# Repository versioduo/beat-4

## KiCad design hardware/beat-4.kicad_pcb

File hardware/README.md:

# beat-4
🧲 4 Channel Solenoid Controller

## Schematic
[PDF](beat-4.pdf)

## Bill Of Materials
[Interactive BOM](https://versioduo.com/view?url=https://raw.githubusercontent.com/versioduo/beat-4/refs/heads/main/hardware/beat-4-bom.html)

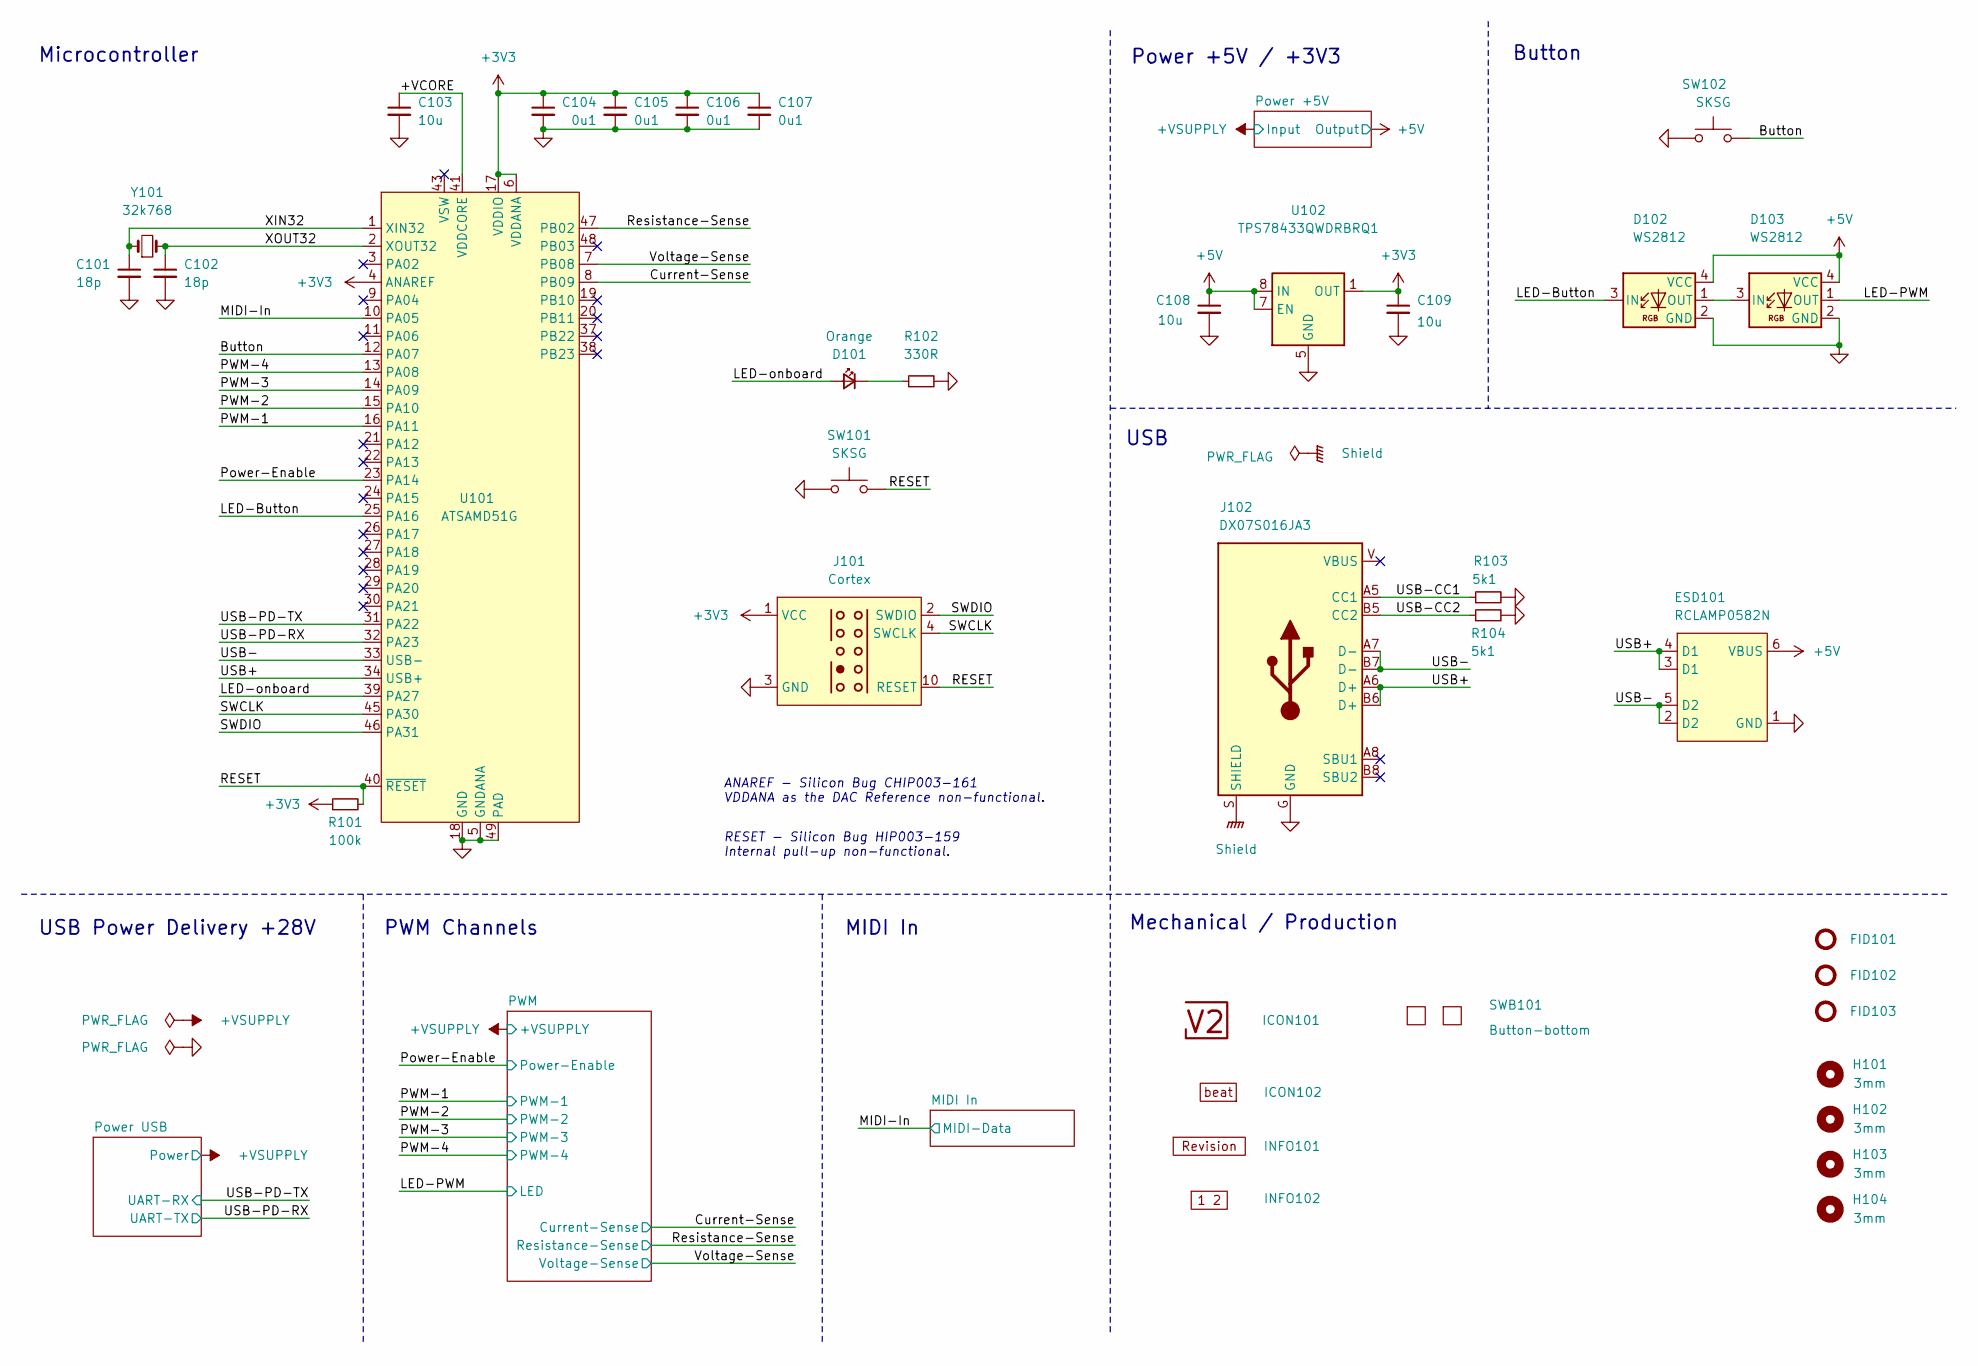
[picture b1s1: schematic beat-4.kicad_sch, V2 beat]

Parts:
C101, C102: 18p; C_1608; Rating 50V; Mouser 810-CGA3E2C0G1H180J
C103: 10u; C_1608; Rating 10V; Mouser 810-C1608X6S1A106M
C104, C105, C106, C107: 0u1; C_1608; Rating 50V; Mouser 810-CGA3E2X7R1H104MA
C108, C109: 10u; C_2012; Rating 25V; Mouser 810-C2012X5R1E106K
D101: Orange; LED_1608; Rating 605nm; Mouser 755-SML-D12D1WT86
D102, D103: WS2812; WS2812-2020; Rating 15mA; LCSC C965555
ESD101: RCLAMP0582N; SLP1210N6; Rating 20kV; Mouser 947-RCLAMP0582N.TCT
FID101, FID102, FID103: Fiducial_Paste; Fiducial_0.5mm_Mask1mm_Paste
H101, H102, H103, H104: 3mm; MountingHole_3mm
ICON101: V2-logo; Logo_Small
ICON102: Board_axis; Board_beat_Small
INFO101: Revision
INFO102: Layer_Numbers-4
J101: Cortex
J102: DX07S016JA3; JAE_DX07S016JA3; Rating USB2.0; Mouser 656-DX07S016JA3R1500
R101: 100k; R_1608; Rating 100mW; Mouser 71-CRCW0603100KFKEAC
R102: 330R; R_1608; Rating 100mW; Mouser 71-CRCW0603330RFKEAC
R103, R104: 5k1; R_1608; Rating 100mW; Mouser 71-CRCW06035K10FKEAC
SW101, SW102: SKSG; Rating 1.6N; Mouser 688-SKSGACE010
SWB101: Button-bottom; PCB_Button-bottom
U101: ATSAMD51G; QFN-48-1EP_7x7mm_P0.5mm_EP5.45x5.45mm_ThermalVias; Rating Cortex-M4F; Mouser 556-ATSAMD51G19AMU
U102: TPS78433QWDRBRQ1; VSON-8-1_3x3mm_P0.65_EP1.65x2.4mm; Rating 300mA; Mouser 595-TPS78433QWDRBRQ1
Y101: 32k768; Crystal_SMD_3215-2Pin_3.2x1.5mm; Rating 10ppm; Mouser 815-ABS0716632.768KT

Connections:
+3V3: C104.1, C105.1, C106.1, C107.1, C109.1, J101.1 (VCC), R101.1, U101.4 (ANAREF), U101.6 (VDDANA), U101.17 (VDDIO), U101.36 (VDDIO), U101.44 (VDDIO), U102.1 (OUT); also elsewhere on the board
+5V: C108.1, D102.4 (VCC), D103.4 (VCC), ESD101.6 (VBUS), U102.6 (EN), U102.7 (EN), U102.8 (IN); also elsewhere on the board
/+VCORE: C103.1, U101.41 (VDDCORE)
/Button: SW102.2, U101.12 (PA07)
/Current-Sense: U101.8 (PB09); also elsewhere on the board
/LED-Button: D102.3 (IN), U101.25 (PA16)
/LED-PWM: D103.1 (OUT); also elsewhere on the board
/LED-onboard: D101.2 (A), U101.39 (PA27)
/MIDI-In: U101.10 (PA05); also elsewhere on the board
/PWM-1: U101.16 (PA11); also elsewhere on the board
/PWM-2: U101.15 (PA10); also elsewhere on the board
/PWM-3: U101.14 (PA09); also elsewhere on the board
/PWM-4: U101.13 (PA08); also elsewhere on the board
/Power-Enable: U101.23 (PA14); also elsewhere on the board
/RESET: J101.10 (RESET), R101.2, SW101.2, U101.40 (~RESET)
/Resistance-Sense: U101.47 (PB02); also elsewhere on the board
/SWCLK: J101.4 (SWCLK), U101.45 (PA30)
/SWDIO: J101.2 (SWDIO), U101.46 (PA31)
/Shield: J102.S (SHIELD)
/USB+: ESD101.3 (D1), ESD101.4 (D1), J102.A6 (D+), J102.B6 (D+), U101.34 (USB+)
/USB-: ESD101.2 (D2), ESD101.5 (D2), J102.A7 (D-), J102.B7 (D-), U101.33 (USB-)
/USB-CC1: J102.A5 (CC1), R103.1
/USB-CC2: J102.B5 (CC2), R104.1
/USB-PD-RX: U101.32 (PA23); also elsewhere on the board
/USB-PD-TX: U101.31 (PA22); also elsewhere on the board
/Voltage-Sense: U101.7 (PB08); also elsewhere on the board
/XIN32: C101.1, U101.1 (XIN32), Y101.1
/XOUT32: C102.1, U101.2 (XOUT32), Y101.2
GND: C101.2, C102.2, C103.2, C104.2, C105.2, C106.2, C107.2, C108.2, C109.2, D102.2 (GND), D103.2 (GND), ESD101.1 (GND), J101.3 (GND), J101.5 (GND), J102.G (GND), R102.2, R103.2, R104.2, SW101.1, SW102.1, U101.5 (GNDANA), U101.18 (GND), U101.35 (GND), U101.42 (GND), U101.49 (PAD), U102.5 (GND), U102.9 (GND); also elsewhere on the board
unnamed: D101.1 (K), R102.1
unnamed: D102.1 (OUT), D103.3 (IN)

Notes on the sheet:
ANAREF - ﻿Silicon Bug CHIP003-161 VDDANA as the DAC Reference non-functional.
PWM Channels
RESET - ﻿Silicon Bug HIP003-159 Internal pull-up non-functional.
Button
Power +5V / +3V3
Mechanical / Production
Microcontroller
MIDI In
USB
USB Power Delivery +28V

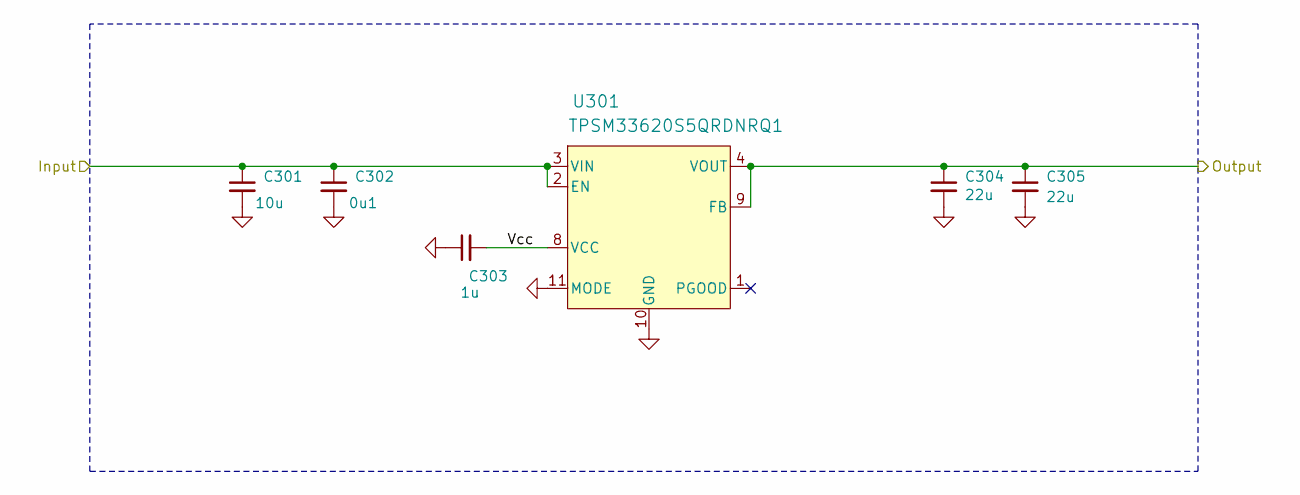
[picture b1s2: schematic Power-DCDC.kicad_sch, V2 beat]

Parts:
C301: 10u; C_3225; Rating 50V; Mouser 810-CNC6P1X7R1H106K2
C302: 0u1; C_1608; Rating 50V; Mouser 810-CGA3E2X7R1H104MA
C303: 1u; C_1608; Rating 50V; Mouser 810-CGA3E3X7R1H105K0
C304, C305: 22u; C_3225; Rating 25V; Mouser 810-CGA6P3X7R1E226M5
U301: TPSM33620S5QRDNRQ1; QFN-11; Rating 2A; Mouser 595-SM33620S5QRDNRQ1

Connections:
+5V: C304.1, C305.1, U301.4 (VOUT), U301.9 (FB); also elsewhere on the board
/+VSUPPLY: C301.1, C302.1, U301.2 (EN), U301.3 (VIN); also elsewhere on the board
/Power +5V/Vcc: C303.2, U301.8 (VCC)
GND: C301.2, C302.2, C303.1, C304.2, C305.2, U301.10 (GND), U301.11 (MODE); also elsewhere on the board

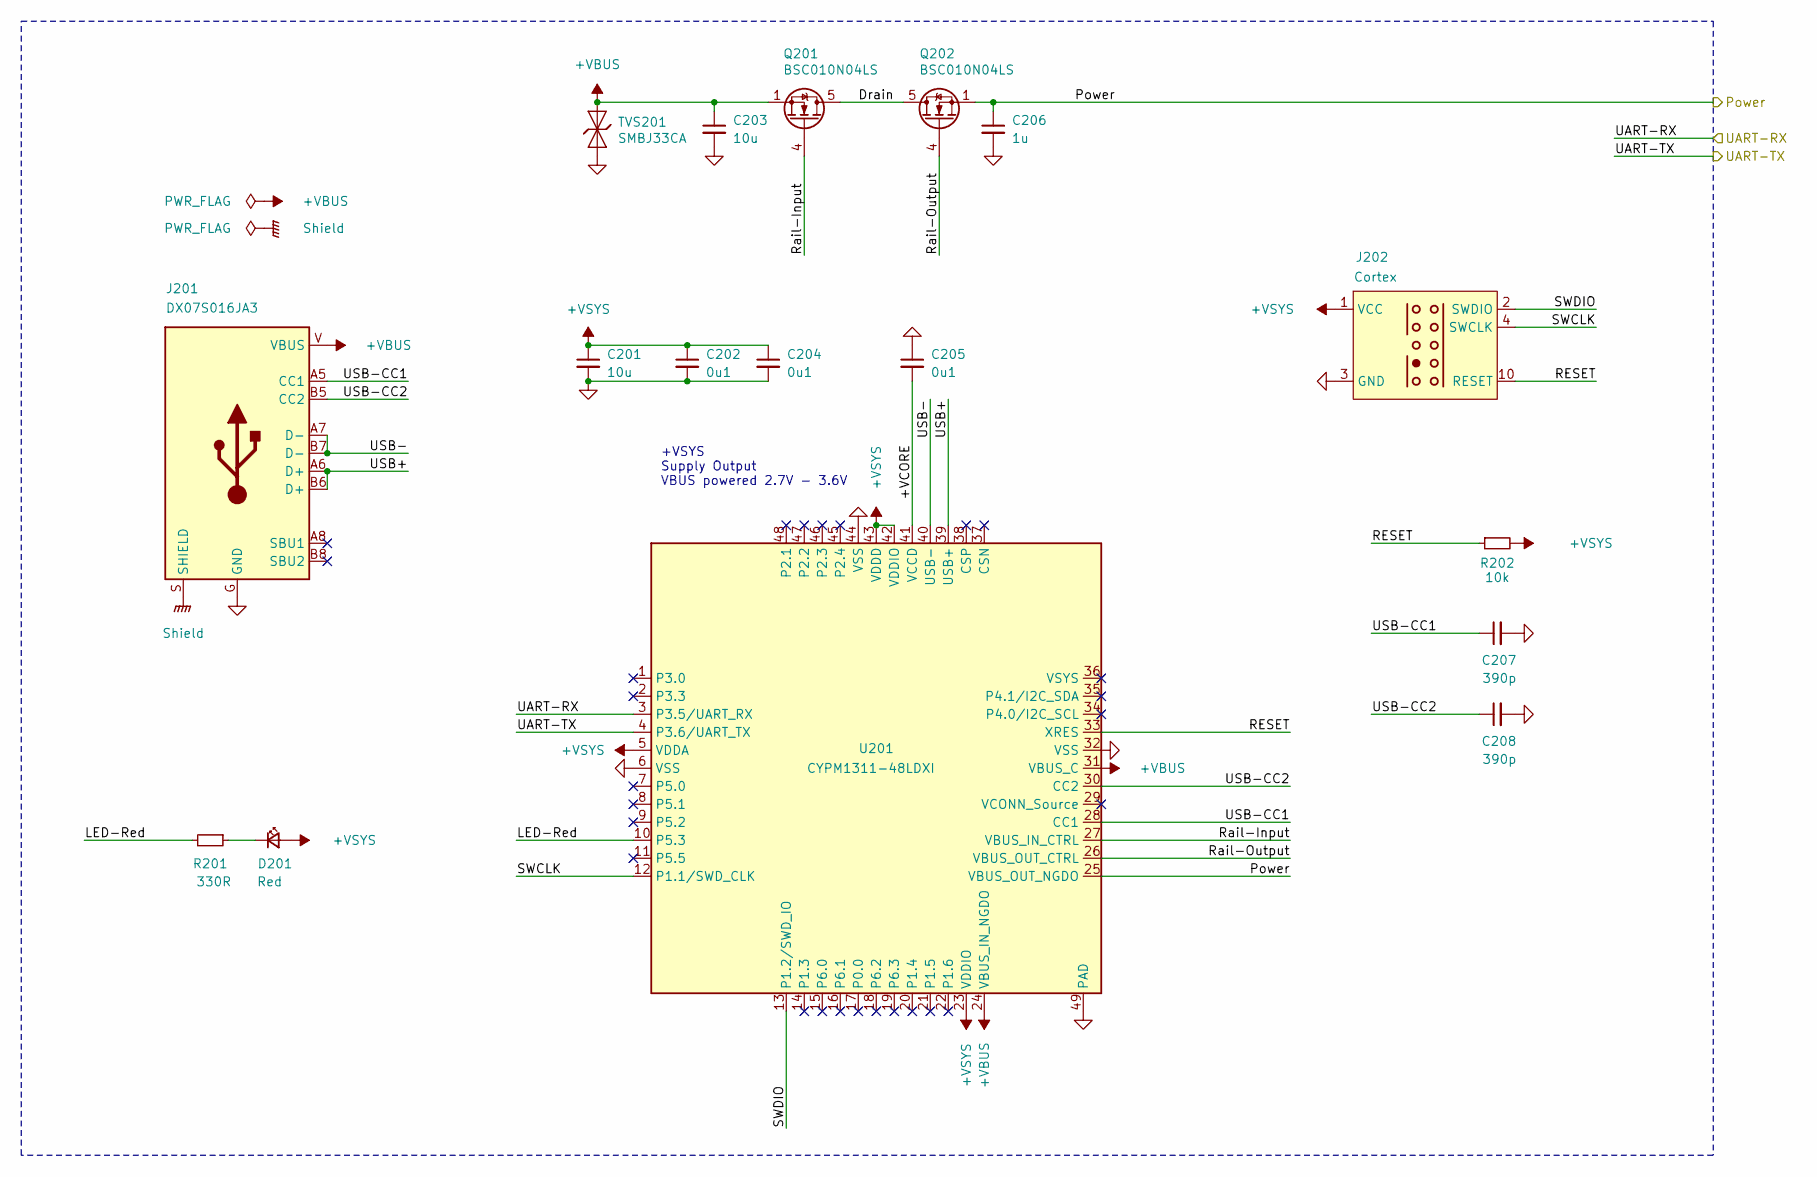
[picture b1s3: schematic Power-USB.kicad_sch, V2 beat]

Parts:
C201: 10u; C_1608; Rating 10V; Mouser 810-C1608X6S1A106M
C202, C204, C205: 0u1; C_1608; Rating 50V; Mouser 810-CGA3E2X7R1H104MA
C203: 10u; C_2012; Rating 25V; Mouser 810-C2012X5R1E106K
C206: 1u; C_1608; Rating 50V; Mouser 810-CGA3E3X7R1H105K0
C207, C208: 390p; C_1608; Rating 50V; Mouser 810-CGA3E2C0G1H391J
D201: Red; LED_1608; Rating 630nm; Mouser 755-SML-D12V1WT86
J201: DX07S016JA3; JAE_DX07S016JA3-PD; Rating USB2.0; Mouser 656-DX07S016JA3R1500
J202: Cortex
Q201, Q202: BSC010N04LS; TDSON-8-FL; Rating 40V; Mouser 726-BSC010N04LS
R201: 330R; R_1608; Rating 100mW; Mouser 71-CRCW0603330RFKEAC
R202: 10k; R_1608; Rating 100mW; Mouser 71-CRCW060310K0FKEAC
TVS201: SMBJ33CA; D_SMB; Rating 33V; Mouser 652-SMBJ33CA-Q
U201: CYPM1311-48LDXI; QFN-48-1EP_6x6mm_P0.4mm_EP4.6x4.6mm; Rating 28V; Mouser 727-CYPM1311-48LDXI

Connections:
/+VSUPPLY: C206.1, Q202.1 (S), U201.25 (VBUS_OUT_NGDO); also elsewhere on the board
/Power USB/+VBUS: C203.1, J201.V (VBUS), Q201.1 (S), TVS201.2 (A), U201.24 (VBUS_IN_NGDO), U201.31 (VBUS_C)
/Power USB/+VCORE: C205.2, U201.41 (VCCD)
/Power USB/+VSYS: C201.1, C202.1, C204.1, D201.2 (A), J202.1 (VCC), R202.2, U201.5 (VDDA), U201.23 (VDDIO), U201.42 (VDDIO), U201.43 (VDDD)
/Power USB/Drain: Q201.5 (D), Q202.5 (D)
/Power USB/LED-Red: R201.2, U201.10 (P5.3)
/Power USB/RESET: J202.10 (RESET), R202.1, U201.33 (XRES)
/Power USB/Rail-Input: Q201.4 (G), U201.27 (VBUS_IN_CTRL)
/Power USB/Rail-Output: Q202.4 (G), U201.26 (VBUS_OUT_CTRL)
/Power USB/SWCLK: J202.4 (SWCLK), U201.12 (P1.1/SWD_CLK)
/Power USB/SWDIO: J202.2 (SWDIO), U201.13 (P1.2/SWD_IO)
/Power USB/Shield: J201.S (SHIELD)
/Power USB/USB+: J201.A6 (D+), J201.B6 (D+), U201.39 (USB+)
/Power USB/USB-: J201.A7 (D-), J201.B7 (D-), U201.40 (USB-)
/Power USB/USB-CC1: C207.1, J201.A5 (CC1), U201.28 (CC1)
/Power USB/USB-CC2: C208.1, J201.B5 (CC2), U201.30 (CC2)
/USB-PD-RX: U201.4 (P3.6/UART_TX); also elsewhere on the board
/USB-PD-TX: U201.3 (P3.5/UART_RX); also elsewhere on the board
GND: C201.2, C202.2, C203.2, C204.2, C205.1, C206.2, C207.2, C208.2, J201.G (GND), J202.3 (GND), J202.5 (GND), TVS201.1 (K), U201.6 (VSS), U201.32 (VSS), U201.44 (VSS), U201.49 (PAD); also elsewhere on the board
unnamed: D201.1 (K), R201.1

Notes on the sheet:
+VSYS Supply Output VBUS powered 2.7V - 3.6V

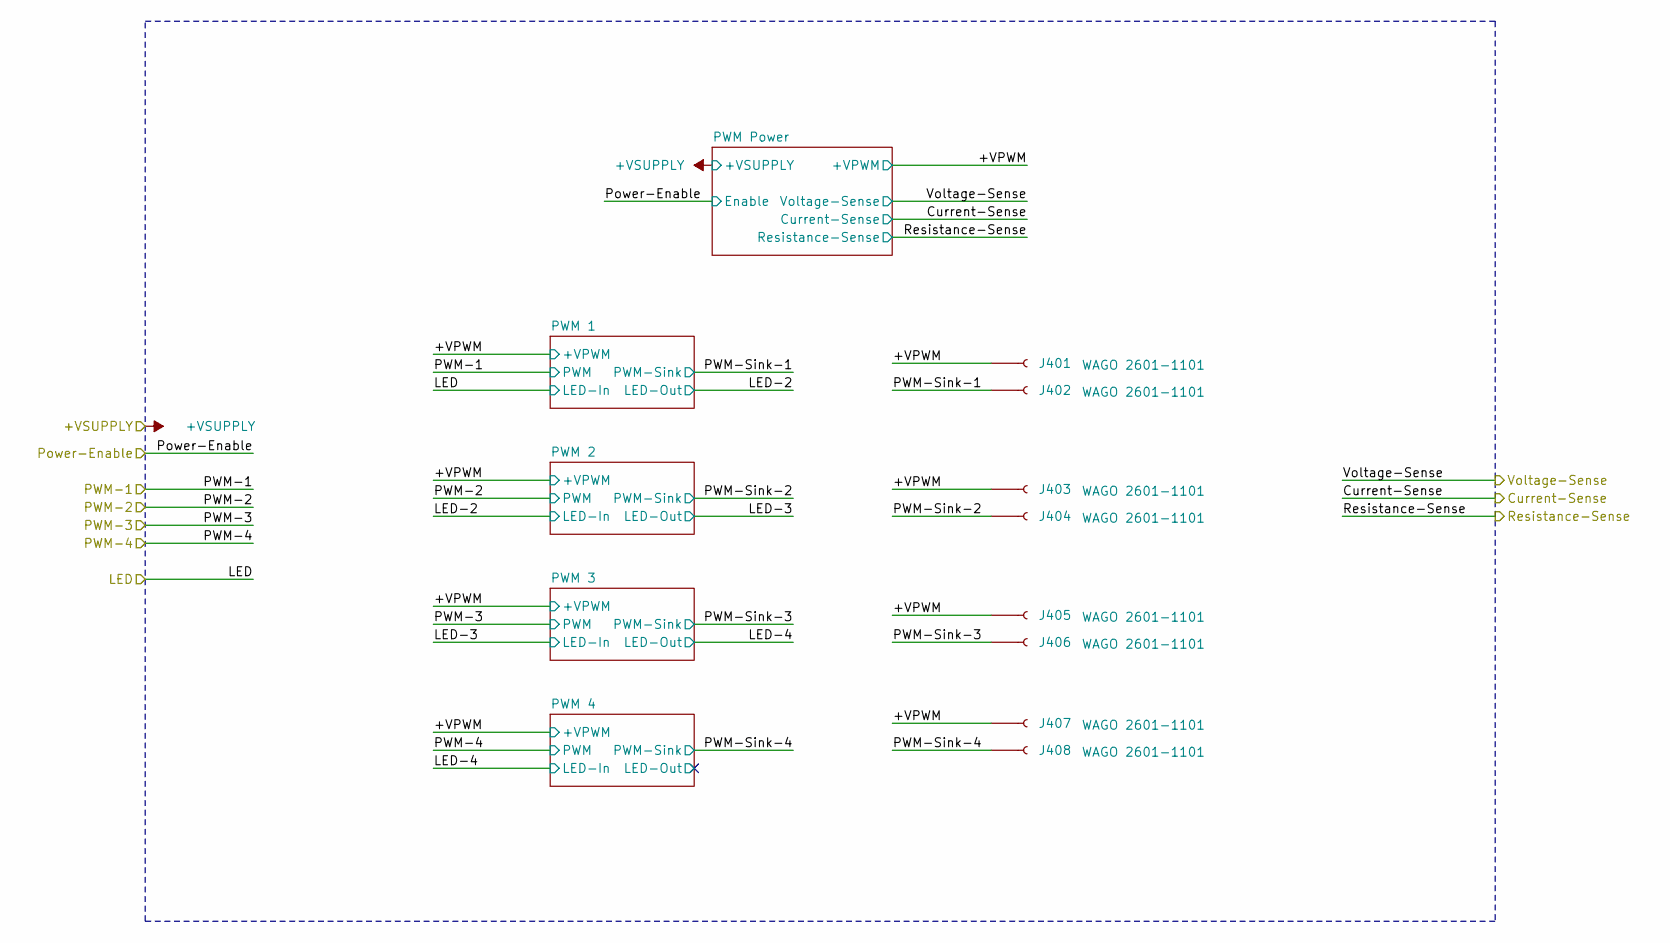
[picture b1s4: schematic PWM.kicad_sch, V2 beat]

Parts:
J401, J402, J403, J404, J405, J406, J407, J408: WAGO 2601-1101; 2601-1101; Rating 17.5A

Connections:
/PWM/+VPWM: J401.1, J403.1, J405.1, J407.1; also elsewhere on the board
/PWM/PWM-Sink-1: J402.1; also elsewhere on the board
/PWM/PWM-Sink-2: J404.1; also elsewhere on the board
/PWM/PWM-Sink-3: J406.1; also elsewhere on the board
/PWM/PWM-Sink-4: J408.1; also elsewhere on the board

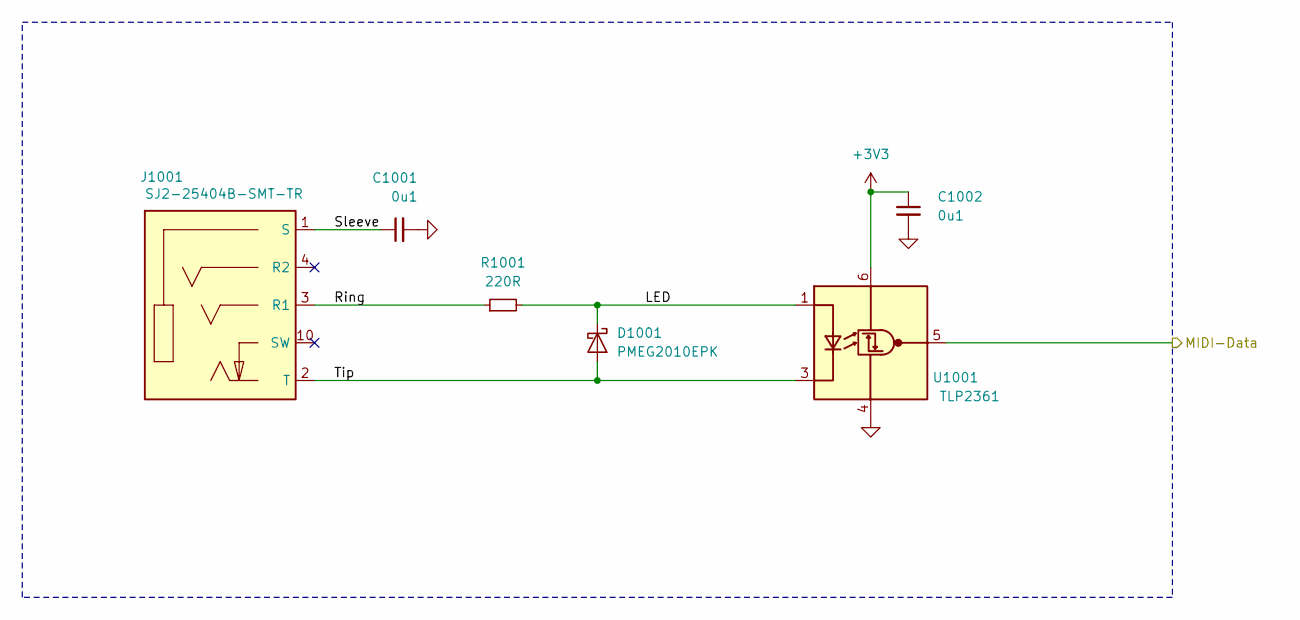
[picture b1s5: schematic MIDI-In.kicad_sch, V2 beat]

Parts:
C1001, C1002: 0u1; C_1608; Rating 50V; Mouser 810-CGA3E2X7R1H104MA
D1001: PMEG2010EPK; D_SOD-1608; Rating 20V; Mouser 771-PMEG2010EPK
J1001: SJ2-25404B-SMT-TR; CUI_SJ2-25404B-SMT-TR; Rating 2.5mm; Mouser 490-SJ2-25404BSMT-TR
R1001: 220R; R_1608; Rating 333mW; Mouser 667-ERJ-PA3F2200V
U1001: TLP2361; SO-5-6_4.55x3.7mm_P1.27mm; Rating 15Mbps; Mouser 757-TLP2361TPRE

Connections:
+3V3: C1002.1, U1001.6 (VDD); also elsewhere on the board
/MIDI In/LED: D1001.1 (K), R1001.2, U1001.1 (A)
/MIDI In/Ring: J1001.3 (R1), R1001.1
/MIDI In/Sleeve: C1001.1, J1001.1 (S)
/MIDI In/Tip: D1001.2 (A), J1001.2 (T), U1001.3 (K)
/MIDI-In: U1001.5 (VO); also elsewhere on the board
GND: C1001.2, C1002.2, U1001.4 (GND); also elsewhere on the board

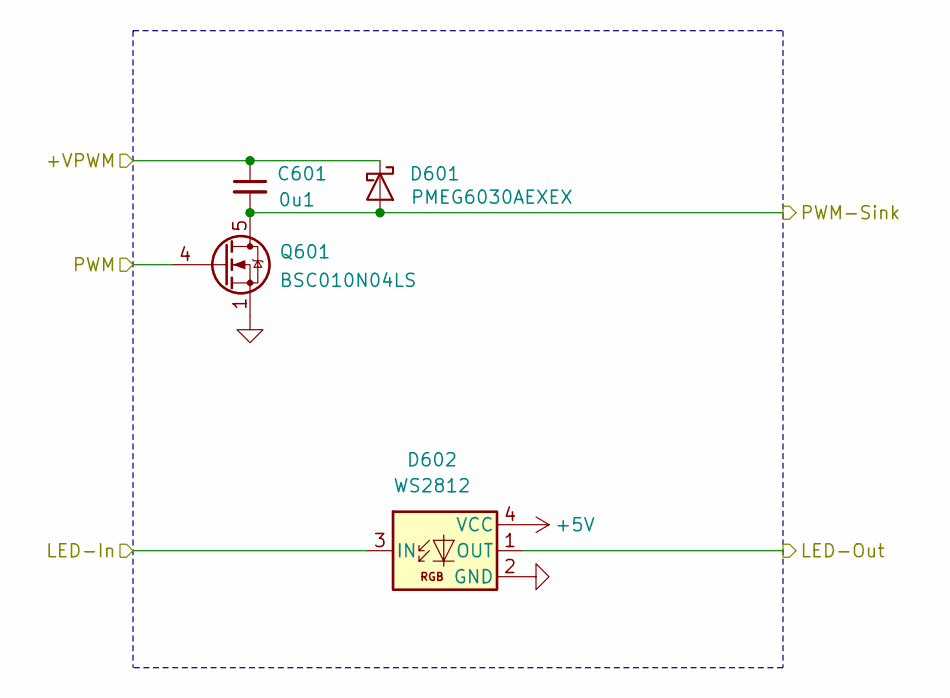
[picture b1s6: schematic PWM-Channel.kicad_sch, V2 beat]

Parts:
C601: 0u1; C_1608; Rating 50V; Mouser 810-CGA3E2X7R1H104MA
D601: PMEG6030AEXEX; D_SOD-123HP; Rating 60V; Mouser 771-PMEG6030AEXEX
D602: WS2812; WS2812-2020; Rating 15mA; LCSC C965555
Q601: BSC010N04LS; TDSON-8-FL; Rating 40V; Mouser 726-BSC010N04LS

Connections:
+5V: D602.4 (VCC); also elsewhere on the board
/LED-PWM: D602.3 (IN); also elsewhere on the board
/PWM-1: Q601.4 (G); also elsewhere on the board
/PWM/+VPWM: C601.1, D601.1 (K); also elsewhere on the board
/PWM/LED-2: D602.1 (OUT); also elsewhere on the board
/PWM/PWM-Sink-1: C601.2, D601.2 (A), Q601.5 (D); also elsewhere on the board
GND: D602.2 (GND), Q601.1 (S); also elsewhere on the board

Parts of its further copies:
C701, C801, C901: 0u1; C_1608; Rating 50V; Mouser 810-CGA3E2X7R1H104MA
D701, D801, D901: PMEG6030AEXEX; D_SOD-123HP; Rating 60V; Mouser 771-PMEG6030AEXEX
D702, D802, D902: WS2812; WS2812-2020; Rating 15mA; LCSC C965555
Q701, Q801, Q901: BSC010N04LS; TDSON-8-FL; Rating 40V; Mouser 726-BSC010N04LS

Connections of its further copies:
+5V: D702.4 (VCC), D802.4 (VCC), D902.4 (VCC); also elsewhere on the board
/PWM-2: Q701.4 (G); also elsewhere on the board
/PWM-3: Q801.4 (G); also elsewhere on the board
/PWM-4: Q901.4 (G); also elsewhere on the board
/PWM/+VPWM: C701.1, C801.1, C901.1, D701.1 (K), D801.1 (K), D901.1 (K); also elsewhere on the board
/PWM/LED-2: D702.3 (IN); also elsewhere on the board
/PWM/LED-3: D702.1 (OUT), D802.3 (IN)
/PWM/LED-4: D802.1 (OUT), D902.3 (IN)
/PWM/PWM 4/LED-Out: D902.1 (OUT)
/PWM/PWM-Sink-2: C701.2, D701.2 (A), Q701.5 (D); also elsewhere on the board
/PWM/PWM-Sink-3: C801.2, D801.2 (A), Q801.5 (D); also elsewhere on the board
/PWM/PWM-Sink-4: C901.2, D901.2 (A), Q901.5 (D); also elsewhere on the board
GND: D702.2 (GND), D802.2 (GND), D902.2 (GND), Q701.1 (S), Q801.1 (S), Q901.1 (S); also elsewhere on the board

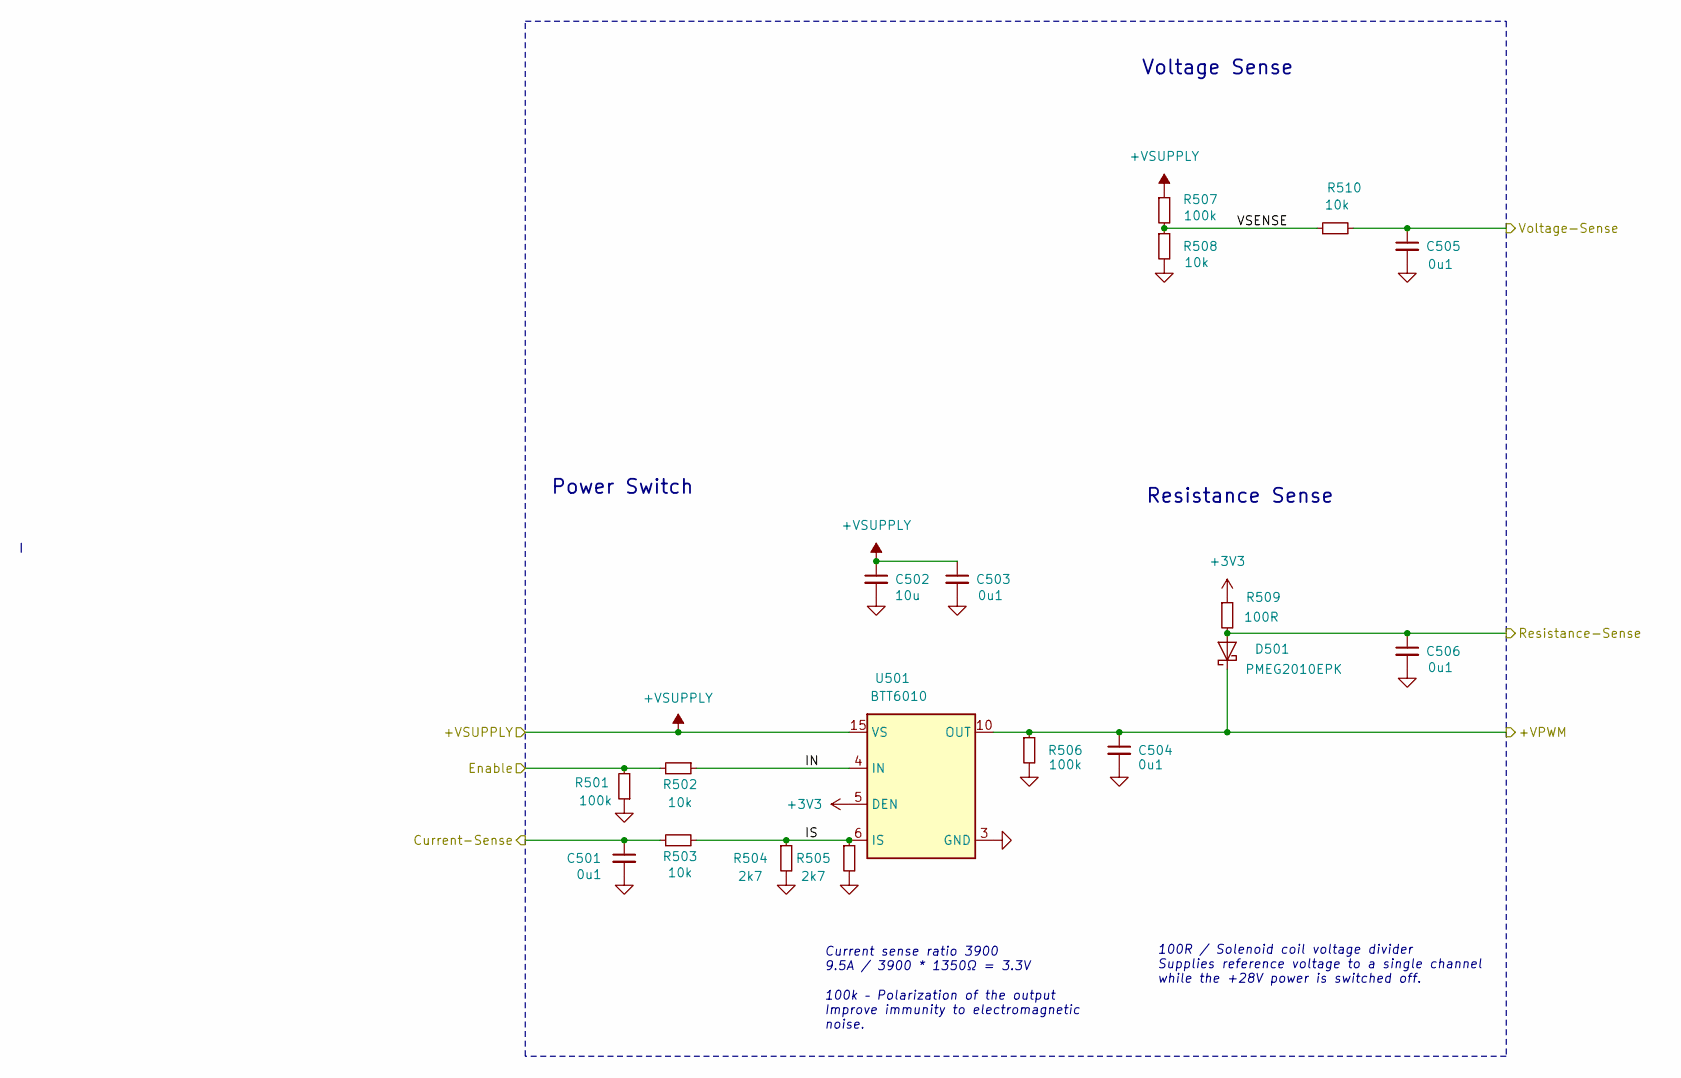
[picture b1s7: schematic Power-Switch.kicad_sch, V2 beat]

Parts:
C501, C503, C504, C505, C506: 0u1; C_1608; Rating 50V; Mouser 810-CGA3E2X7R1H104MA
C502: 10u; C_3225; Rating 50V; Mouser 810-CNC6P1X7R1H106K2
D501: PMEG2010EPK; D_SOD-1608; Rating 20V; Mouser 771-PMEG2010EPK
R501, R506, R507: 100k; R_1608; Rating 100mW; Mouser 71-CRCW0603100KFKEAC
R502, R503, R508, R510: 10k; R_1608; Rating 100mW; Mouser 71-CRCW060310K0FKEAC
R504, R505: 2k7; R_1608; Rating 100mW; Mouser 71-CRCW06032K70FKEAC
R509: 100R; R_1608; Rating 330mW; Mouser 71-CRCW0603100RFKEAH
U501: BTT6010; PG-TDS0-14; Rating 36V; Mouser 726-BTT60101ERBXUMA1

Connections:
+3V3: R509.1, U501.5 (DEN); also elsewhere on the board
/+VSUPPLY: C502.1, C503.1, R507.1, U501.15 (VS); also elsewhere on the board
/Current-Sense: C501.1, R503.1; also elsewhere on the board
/PWM/+VPWM: C504.1, D501.1 (K), R506.1, U501.10 (OUT), U501.11 (OUT), U501.12 (OUT); also elsewhere on the board
/PWM/PWM Power/IN: R502.1, U501.4 (IN)
/PWM/PWM Power/IS: R503.2, R504.1, R505.1, U501.6 (IS)
/PWM/PWM Power/VSENSE: R507.2, R508.1, R510.1
/Power-Enable: R501.2, R502.2; also elsewhere on the board
/Resistance-Sense: C506.1, D501.2 (A), R509.2; also elsewhere on the board
/Voltage-Sense: C505.1, R510.2; also elsewhere on the board
GND: C501.2, C502.2, C503.2, C504.2, C505.2, C506.2, R501.1, R504.2, R505.2, R506.2, R508.2, U501.3 (GND); also elsewhere on the board

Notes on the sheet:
100k – Polarization of the output Improve immunity to electromagnetic noise.
Current sense ratio 3900 9.5A / 3900 * 1350Ω = 3.3V
Voltage Sense
Power Switch
100R / Solenoid coil voltage divider Supplies reference voltage to a single channel while the +28V power is switched off.
Resistance Sense

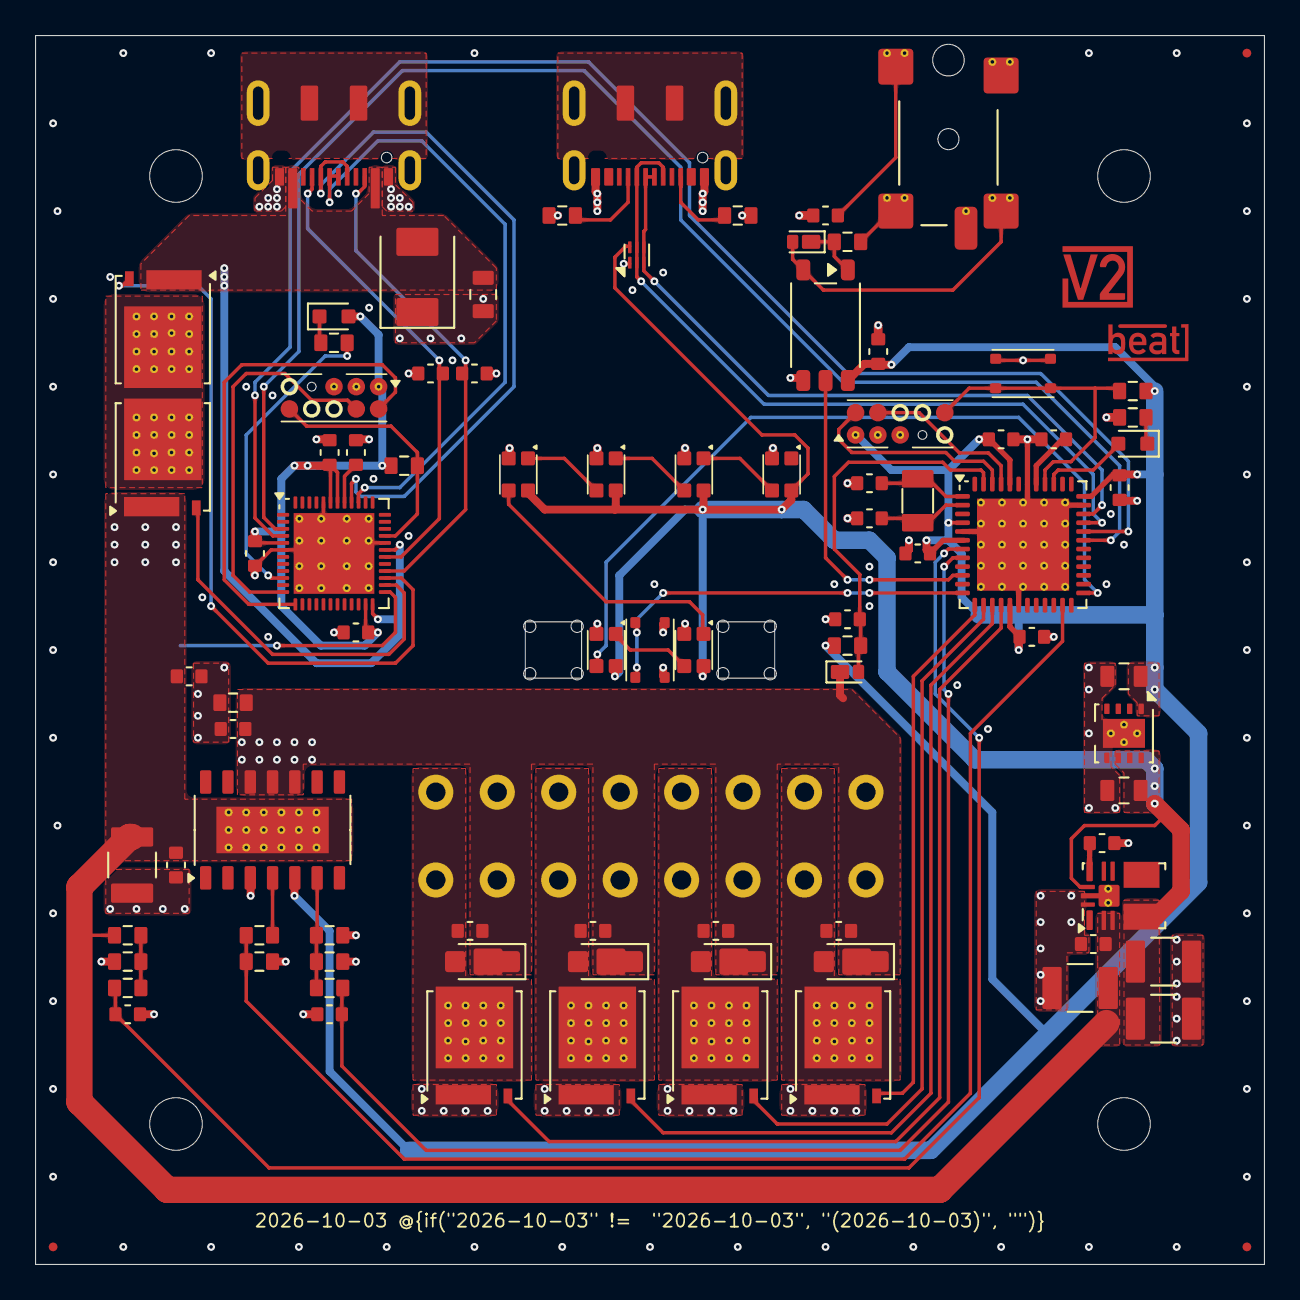
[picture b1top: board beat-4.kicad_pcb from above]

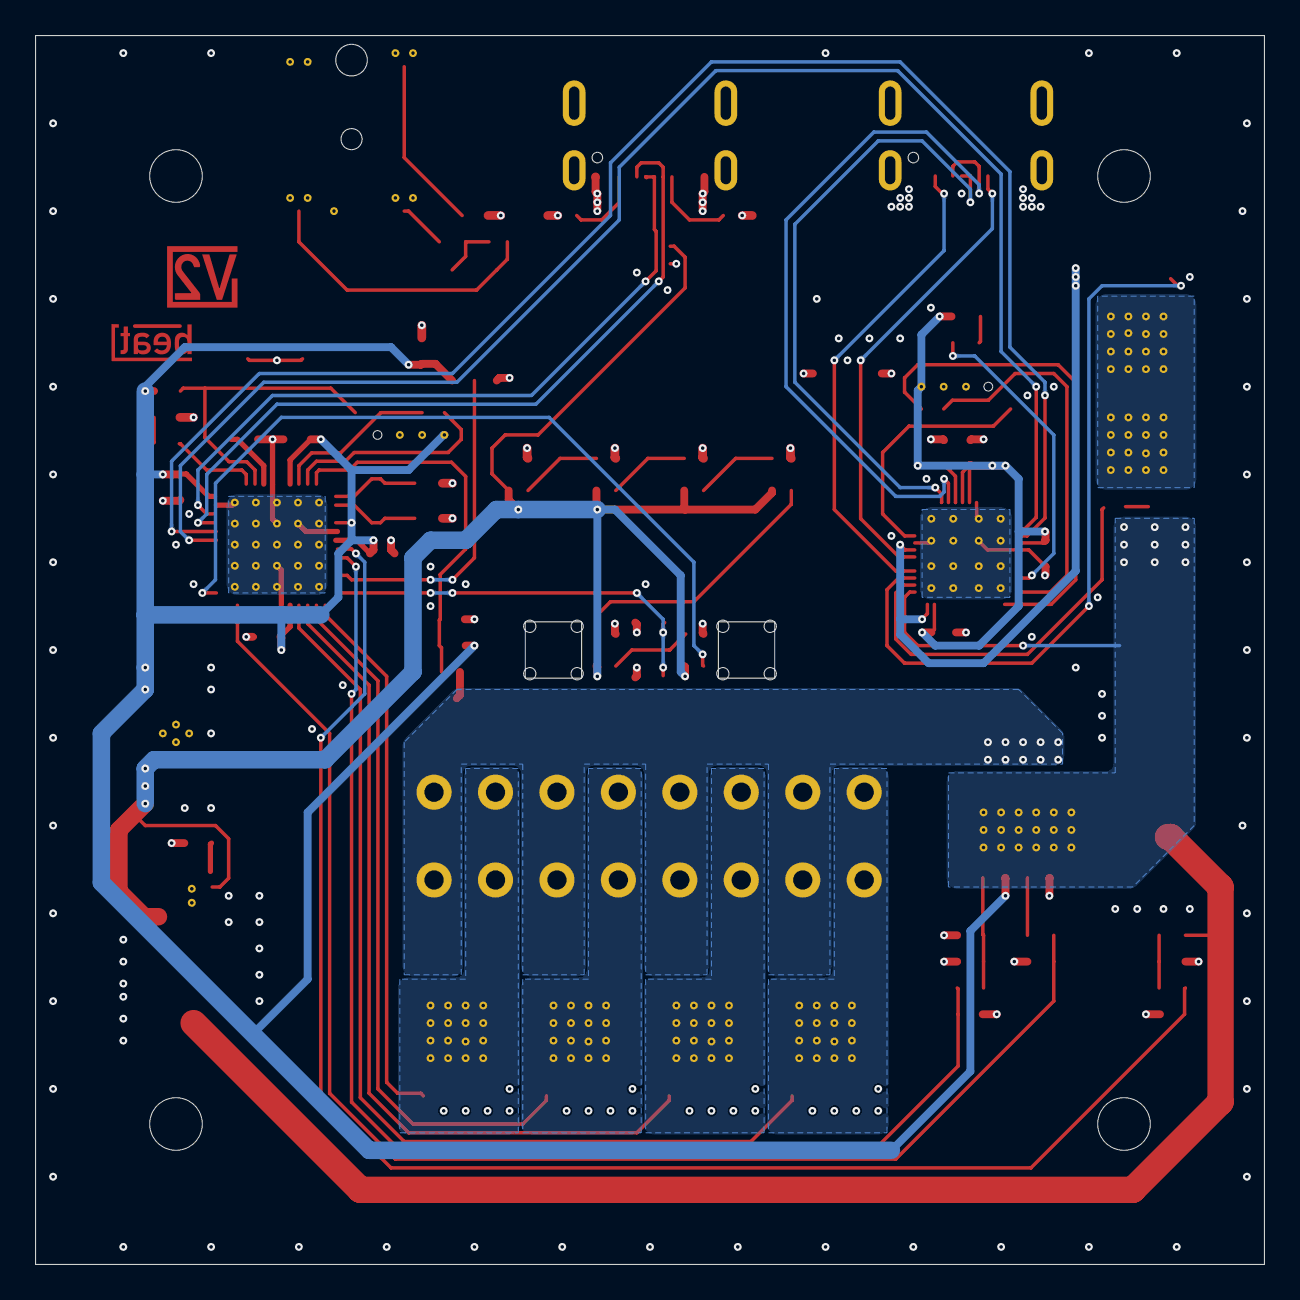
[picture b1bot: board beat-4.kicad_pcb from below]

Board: 4 copper layers, 70.0 x 70.0 mm, 107 parts (8 on the bottom side), 62 nets.
